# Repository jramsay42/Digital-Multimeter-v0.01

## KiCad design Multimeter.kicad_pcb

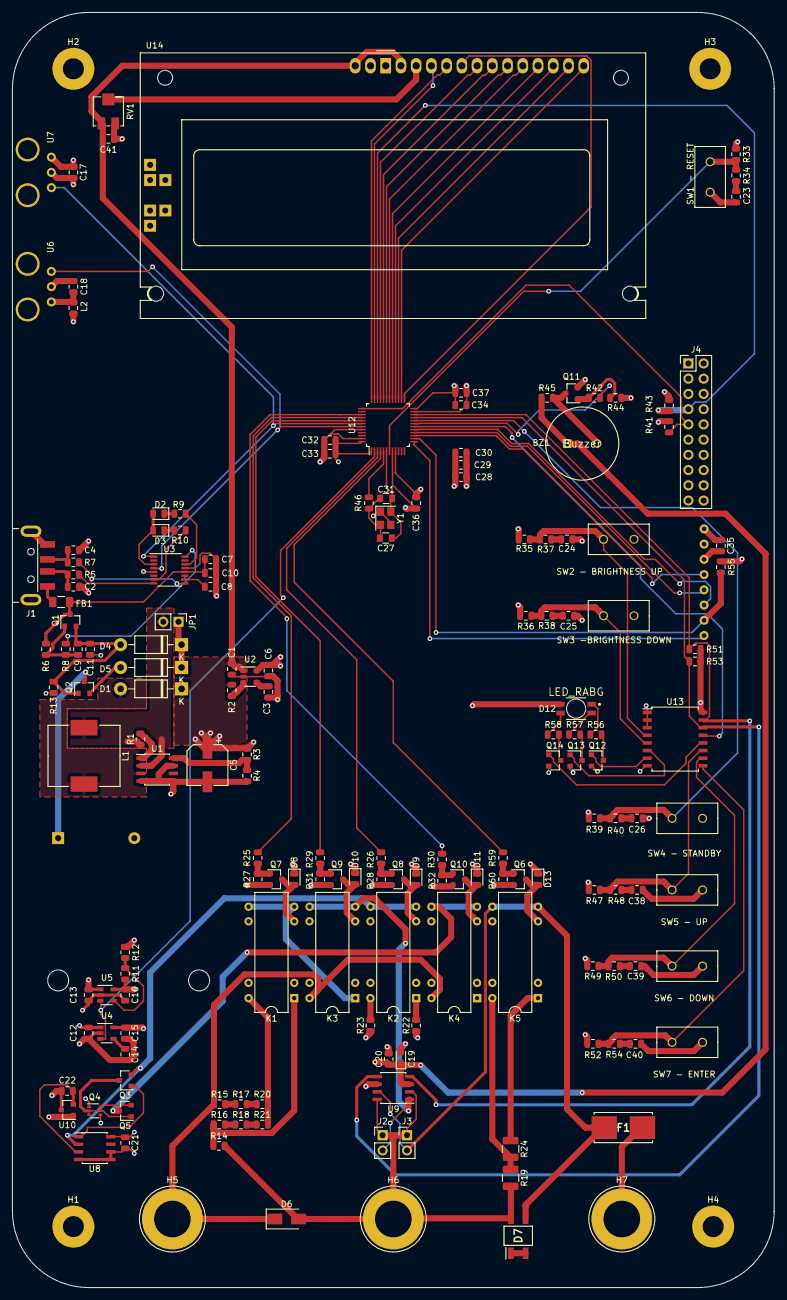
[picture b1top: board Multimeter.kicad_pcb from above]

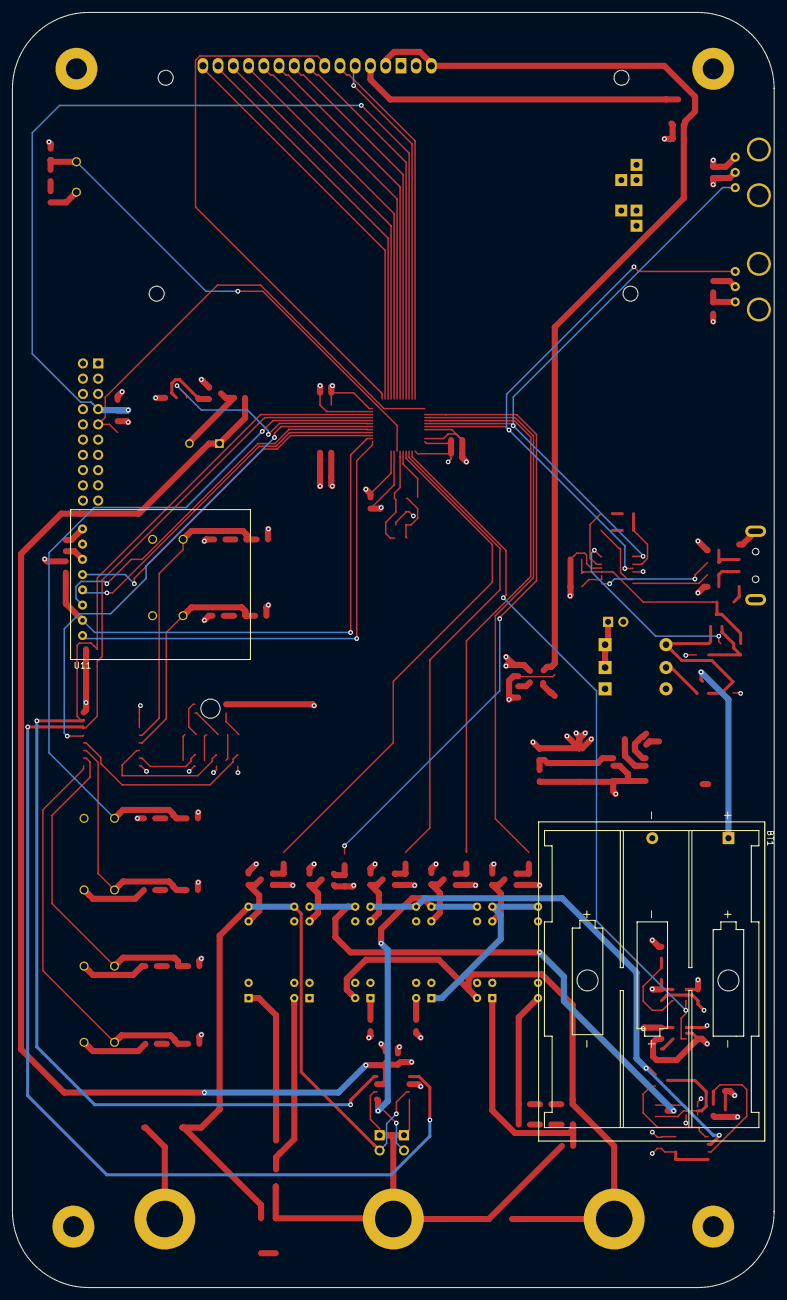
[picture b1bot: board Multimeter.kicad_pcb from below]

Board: 4 copper layers, 127.0 x 212.6 mm, 174 parts (2 on the bottom side), 126 nets.

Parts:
BT1: Battery Holder; Keystone_2479_3xAAA
BZ1: Buzzer; TDK-PS1240P02BT-0
C1, C7, C8, C9, C11, C17, C18, C21, C23, C24, C25, C26, C35, C38, C39, C40, C41: 0.1u; C_0805_2012Metric
C2, C4: 47p; C_0805_2012Metric
C3, C14: 0.01u; C_0805_2012Metric
C5: 100u, Low ESR Al; CP_Elec_6.3x5.4
C6, C12, C13, C15, C16, C20: 0.1u, Ceramic; C_0805_2012Metric
C10: 4.7u; C_0805_2012Metric
C19: 10u, Tantalum; CP_EIA-2012-12_Kemet-R_Pad1.30x1.05mm_HandSolder
C22: 1u; C_0805_2012Metric
C27, C31: 27p; C_0805
C28: 10u; C_0805_2012Metric
C29, C30, C32, C33, C34, C36, C37: 100n; C_0805_2012Metric
D1, D4, D5: 1N5818; D_DO-41_SOD81_P10.16mm_Horizontal
D2, D3: LED; D_0805_2012Metric
D6: D_TVS; D_SMA
D7: MB8S; SOP245P670X290-4N
D8, D9, D10, D11, D13: D; D_0805_2012Metric
D12: LED_RABG; SunLED-XZMDKCBDDG45S-9-MFG
F1: Fuse - 500 mA; 0154500DRT
FB1: 600 Ohms @ 100 MHz, 1.5A, 80mOhm; R_1206_3216Metric
H1, H2, H3, H4: MountingHole_Pad; MountingHole_3.5mm_Pad
H5, H6, H7: MountingHole_Pad; Banana_Jack_1Pin
J1: USB_A; USB_A_CNCTech_1001-011-01101_Horizontal
J2, J3: Conn_01x02_Male; PinHeader_1x02_P2.54mm_Vertical
J4: Conn_ARM_JTAG_SWD_20; PinHeader_2x10_P2.54mm_Vertical
JP1: Jumper_2_Open; PinHeader_1x02_P2.54mm_Vertical
K1, K2, K3, K4, K5: DIPxx-1Cxx-51x; Relay_StandexMeder_DIP_LowProfile
L1: 150uH; L_Wuerth_HCM-1240
L2: 47u; L_0805_2012Metric
Q1, Q2: IRLML6402; SOT-23
Q3: BC818; SOT-23
Q4: BC857BDW1; SOT-363_SC-70-6
Q5: BC856; SOT-23
Q6, Q7, Q8, Q9, Q10, Q11, Q12, Q13, Q14: 2N7002; SOT-23
R1, R2, R4, R13, R33, R35, R36, R39, R41, R43, R47, R49, R51, R52, R53, R55: 10k; R_0805_2012Metric
R3: 31.6k; R_0805_2012Metric
R5, R7: 27; R_0805_2012Metric
R6, R27, R28, R31, R32, R44, R60: 100k; R_0805_2012Metric
R8, R34, R37, R38, R40, R45, R48, R50, R54: 1k; R_0805_2012Metric
R9, R10, R56, R57, R58: 330; R_0805_2012Metric
R11: 75k, 0.1%; R_0805_2012Metric
R12: 23.7k, 0.1%; R_0805_2012Metric
R14: 180k, 0.1%; R_0805_2012Metric
R15: 620k, 1%; R_0805_2012Metric
R16: 2k, 0.1%; R_0805_2012Metric
R17: 27k, 0.1%; R_0805_2012Metric
R18: 10k, 0.1%; R_0805_2012Metric
R19: 1, 1/4 W; R_1210_3225Metric
R20: 1k, 0.1%; R_0805_2012Metric
R21: 240k, 0.1%; R_0805_2012Metric
R22: 200, 5%; R_0805_2012Metric
R23: 200k, 5%; R_0805_2012Metric
R24: 24, 1/4W; R_1210_3225Metric
R25, R26, R29, R30, R42, R46, R59: 220; R_0805_2012Metric
RV1: R_POT_TRIM_US; Potentiometer_Bourns_3214J_Horizontal
SW1 - RESET, SW2 - BRIGHTNESS UP, SW3 -BRIGHTNESS DOWN, SW4 - STANDBY, SW5 - UP, SW6 - DOWN, SW7 - ENTER: SW_Push; SPST-800SP9B6M2RE
U1: ADP1108AN; SOIC-8_3.9x4.9mm_P1.27mm
U2, U4: TPS73633DBV; SOT-23-5
U3: FT230XS; SSOP-16_3.9x4.9mm_P0.635mm
U5: TPS73601DBV; SOT-23-5
U6: PLR135; Everlight - PLR135
U7: PLT133; Everlight - PLR135
U8: TL072; SOIC-8_3.9x4.9mm_P1.27mm
U9: MCP3422; SOIC-8_3.9x4.9mm_P1.27mm
U10: MAX6100; SOT-23
U11: MicroSD_Breakout
U12: STM32F030C6Tx; LQFP-48_7x7mm_P0.5mm
U13: PCF8574; SOIC-16W_7.5x10.3mm_Pitch1.27mm
U14: RC1602A
Y1: 16 MHz; Crystal_SMD_3225-4Pin_3.2x2.5mm

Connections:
+3.3VA: BZ1.1, C15.1, C19.1, C20.1, R45.1, U4.5, U9.3, U10.1
+3V3: C6.1, C17.2, C28.1, C29.1, C30.1, C32.1, C33.1, C34.1, C36.1, C37.1, J4.1, J4.2, L2.1, R33.1, R35.1, R36.1, R39.1, R41.1, R43.1, R47.1, R49.1, R51.1, R52.1, R53.1, R55.1, U2.5, U7.2, U12.1, U12.9, U12.24, U12.48, U13.16
+5V: C1.1, C5.1, C12.1, C13.1, C35.1, C41.1, D1.1, D12.2, R2.2, R3.1, RV1.3, U2.1, U4.1, U5.1, U11.8, U14.2, U14.15
+5VA: C16.1, C21.1, D8.1, D9.1, D10.1, D11.1, D13.1, K1.2, K2.2, K3.2, K4.2, K5.2, Q4.1, Q4.4, R11.1, U5.5, U8.8
/Measurement/CSC: R59.1, U12.4
/Measurement/I: F1.2, H7.1
/Measurement/RMC: R30.1, U12.39
/Measurement/RSC: R26.1, U12.3
/Measurement/SCL: R53.2, U9.5, U12.21, U13.14
/Measurement/SDA: R51.2, U9.4, U12.22, U13.15
/Measurement/VSC_1: R25.1, U12.40
/Measurement/VSC_2: R29.1, U12.41
/Measurement/Vref: C22.1, U8.3, U10.2
/PowerAndComms/ANALOG_ENABLE: U4.3, U5.3, U12.2
/PowerAndComms/D+: C4.1, J1.3, R7.2
/PowerAndComms/D-: C2.1, J1.2, R5.2
/PowerAndComms/PWREN: R8.1, U3.16
/PowerAndComms/RXD: U3.4, U6.1, U12.43
/PowerAndComms/TXD: U3.1, U7.3, U12.42
/Processing/!INT: U12.18, U13.13
/Processing/BRIGHTNESS_DOWN: R36.2, R38.2, SW3 -BRIGHTNESS DOWN.1, U13.5
/Processing/BRIGHTNESS_UP: R35.2, R37.2, SW2 - BRIGHTNESS UP.1, U13.4
/Processing/BUZZER_1: R42.2, U12.19
/Processing/CD: U11.1, U12.13
/Processing/CLK: U11.5, U12.15
/Processing/CS: R55.2, U11.2, U12.14
/Processing/DB0: U12.33, U14.7
/Processing/DB1: U12.32, U14.8
/Processing/DB2: U12.31, U14.9
/Processing/DB3: U12.30, U14.10
/Processing/DB4: U12.29, U14.11
/Processing/DB5: U12.28, U14.12
/Processing/DB6: U12.27, U14.13
/Processing/DB7: U12.26, U14.14
/Processing/E: U12.25, U14.6
/Processing/LED_B: Q14.1, U13.12
/Processing/LED_G: Q13.1, U13.6
/Processing/LED_R: Q12.1, U13.7
/Processing/MENU_DOWN: R49.2, R50.2, SW6 - DOWN.1, U13.10
/Processing/MENU_ENTER: R52.2, R54.2, SW7 - ENTER.1, U13.9
/Processing/MENU_UP: R47.2, R48.2, SW5 - UP.1, U13.11
/Processing/MISO: U11.4, U12.16
/Processing/MOSI: U11.3, U12.17
/Processing/RESET: R33.2, R34.2, SW1 - RESET.1, U12.7
/Processing/RS: U12.35, U14.4
/Processing/RW: U12.36, U14.5
/Processing/STANDBY: R39.2, R40.2, SW4 - STANDBY.1, U12.20
/Processing/SWDCLK: J4.9, R41.2, U12.37
/Processing/SWDIO: J4.7, R43.2, U12.34
ADC1+: J2.2, K3.7, K3.8, U9.1
ADC1-: D6.2, D7.4, H6.1, J2.1, J3.1, R14.2, R19.2, U9.2, U9.8
ADC2+: D7.3, F1.1, J3.2, K5.7, K5.8, U9.7
CURRENT_NC: K5.1, R24.1
CURRENT_NO: K5.14, R19.1, R24.2
GNDA: C19.2, C20.2, C21.2, C22.2, H1.1, H4.1, R22.1, R23.1, U8.4, U8.5, U8.6, U9.6, U10.3
GNDD: C17.1, C18.2, C23.2, C24.2, C25.2, C26.2, C28.2, C29.2, C30.2, C32.2, C33.2, C34.2, C35.2, C36.2, C37.2, C38.2, C39.2, C40.2, C41.2, H2.1, H3.1, J4.4, J4.6, J4.8, J4.10, J4.12, J4.14, J4.16, J4.18, J4.20, Q6.2, Q7.2, Q8.2, Q9.2, Q10.2, Q11.2, Q12.2, Q13.2, Q14.2, R27.1, R28.1, R31.1, R32.1, R44.1, R60.1, RV1.1, SW1 - RESET.2, SW2 - BRIGHTNESS UP.2, SW3 -BRIGHTNESS DOWN.2, SW4 - STANDBY.2, SW5 - UP.2, SW6 - DOWN.2, SW7 - ENTER.2, U6.2, U7.1, U11.6, U12.8, U12.23, U12.44, U12.47, U13.1, U13.2, U13.3, U13.8, U14.1, U14.16, Y1.1, Y1.3
GNDREF: BT1.2, C1.2, C2.2, C3.2, C4.2, C5.2, C6.2, C7.2, C8.2, C10.2, C11.2, C12.2, C13.2, C14.2, C15.2, C16.2, J1.4, J1.5, R4.2, R12.2, R13.2, U1.4, U1.5, U1.7, U2.2, U3.5, U3.13, U4.2, U5.2
Iout: D6.1, H5.1, K3.14, K4.14, R15.1
IoutCommon: K4.7, K4.8, Q5.3
unnamed: BZ1.2, Q11.3, R45.2
unnamed: C3.1, U2.4
unnamed: C8.1, U3.10, U3.11
unnamed: C9.2, Q1.1, R6.1, R8.2
unnamed: C7.1, C10.1, FB1.1, Q1.3, R6.2, U3.12
unnamed: C14.1, U4.4
unnamed: C18.1, L2.2, U6.3
unnamed: C23.1, R34.1
unnamed: C24.1, R37.1
unnamed: C25.1, R38.1
unnamed: C26.1, R40.1
unnamed: C27.1, C31.1, R46.2, Y1.2
unnamed: C27.2, C31.2, U12.6, Y1.4
unnamed: C38.1, R48.1
unnamed: C39.1, R50.1
unnamed: C40.1, R54.1
unnamed: D1.2, L1.2, U1.3
unnamed: D2.1, R9.2
unnamed: D2.2, D3.2, U3.3
unnamed: D3.1, R10.2
unnamed: D4.1, D5.1, JP1.1
unnamed: D5.2, Q2.2
unnamed: D7.1, D7.2
unnamed: D8.2, K1.6, Q7.3
unnamed: D9.2, K2.6, Q8.3
unnamed: D10.2, K3.6, Q9.3
unnamed: D11.2, K4.6, Q10.3
unnamed: D12.1, R56.1
unnamed: D12.3, R58.1
unnamed: D12.4, R57.1
unnamed: D13.2, K5.6, Q6.3
unnamed: FB1.2, J1.1
unnamed: Q3.1, U8.1
unnamed: Q3.3, Q4.2, Q4.3, Q4.5, Q5.1
unnamed: Q4.6, Q5.2
unnamed: Q6.1, R59.2, R60.2
unnamed: Q7.1, R25.2, R27.2
unnamed: Q8.1, R26.2, R28.2
unnamed: Q9.1, R29.2, R31.2
unnamed: Q10.1, R30.2, R32.2
unnamed: Q11.1, R42.1, R44.2
unnamed: Q12.3, R56.2
unnamed: Q13.3, R57.2
unnamed: Q14.3, R58.2
unnamed: R1.2, U1.1
unnamed: R2.1, U2.3
unnamed: R3.2, R4.1, U1.8
unnamed: R5.1, U3.8
unnamed: R7.1, U3.9
unnamed: R9.1, U3.14
unnamed: R10.1, U3.7
unnamed: R11.2, R12.1, U5.4
unnamed: R15.2, R17.1
unnamed: R16.2, R18.1
unnamed: R17.2, R20.1
unnamed: R18.2, R21.1
unnamed: R46.1, U12.5
unnamed: RV1.2, U14.3
RSC_COM: K2.7, K2.8, Q3.2, U8.2
RSC_NC: K2.1, R22.2
RSC_NO: K2.14, R23.2
VSC_1_COM: K1.7, K1.8, K3.1
VSC_1_NC: K1.1, R14.1, R16.1
VSC_1_NO: K1.14, R20.2, R21.2
Vbat: BT1.1, Q2.3
Vbus: C9.1, C11.1, D4.2, Q1.2, Q2.1, R13.1
Vin: JP1.2, L1.1, R1.1, U1.2
